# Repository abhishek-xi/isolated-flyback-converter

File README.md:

# Isolated Flyback Converter

## Overview

This repository contains the complete design of an isolated flyback DC-DC converter developed using KiCad. The project includes the schematic, PCB layout, manufacturing files, and supporting documentation required for fabrication and assembly.

The converter provides galvanic isolation between the input and output stages, making it suitable for embedded systems, industrial electronics, sensor interfaces, and low-power isolated supply applications.

---

## Features

- Isolated DC-DC power conversion
- Flyback converter topology
- Compact PCB design
- Designed using KiCad
- Manufacturing-ready Gerber files

---

## Design Files

| File | Description |
|--------|------------|
| prj1.kicad_sch | Circuit schematic |
| prj1.kicad_pcb | PCB layout |
| prj1.kicad_pro | KiCad project file |
| Gerbers | PCB manufacturing files |

---

## Applications

- Embedded Systems
- Industrial Electronics
- Sensor Interfaces
- Isolated Communication Systems
- Power Supply Modules
- IoT Devices

---

## Tools Used

- KiCad
- Git
- GitHub

---

## Future Improvements

- Transformer optimization
- Efficiency characterization
- Thermal analysis
- EMC/EMI validation
- Hardware testing documentation

---

## Author

**Abhishek B Kumbar**

Electronics and Communication Engineering

---

## License

This project is released under the MIT License.

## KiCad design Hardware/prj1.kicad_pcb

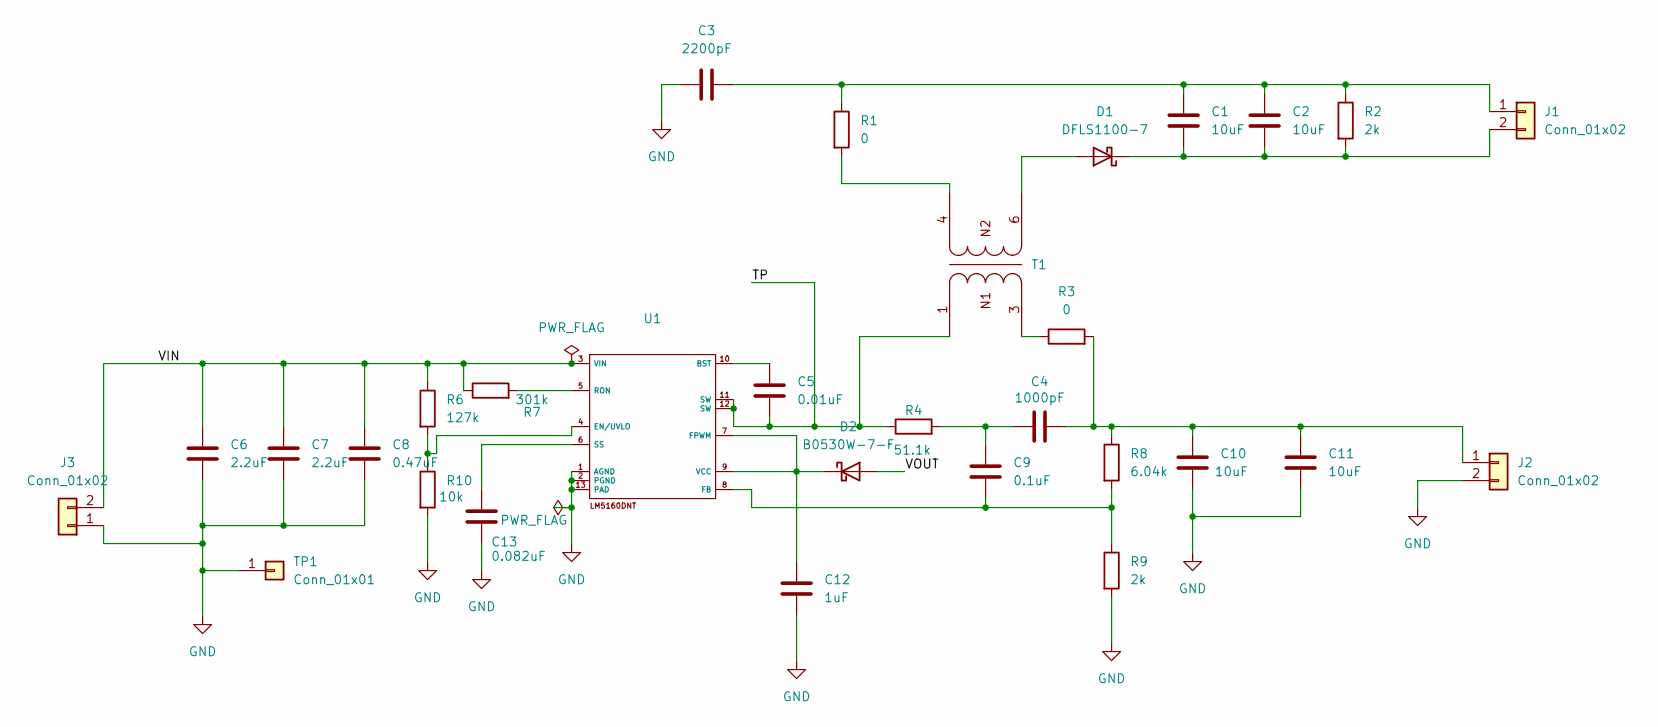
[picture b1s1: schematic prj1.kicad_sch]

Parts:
C1, C2, C10, C11: 10uF; C_1206_3216Metric
C3: 2200pF; C_0603_1608Metric
C4: 1000pF; C_0603_1608Metric
C5: 0.01uF; C_0603_1608Metric
C6, C7: 2.2uF; C_0805_2012Metric
C8: 0.47uF; C_0805_2012Metric
C9: 0.1uF; C_0603_1608Metric
C12: 1uF; C_0603_1608Metric
C13: 0.082uF; C_0603_1608Metric
D1: DFLS1100-7; D_SMA
D2: B0530W-7-F; D_SMA
J1, J2, J3: Conn_01x02; TerminalBlock_Phoenix_MKDS-1,5-2-5.08_1x02_P5.08mm_Horizont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
R1, R3: 0; R_0603_1608Metric
R2, R9: 2k; R_0603_1608Metric
R4: 51.1k; R_0603_1608Metric
R6: 127k; R_0603_1608Metric
R7: 301k; R_0603_1608Metric
R8: 6.04k; R_0603_1608Metric
R10: 10k; R_0603_1608Metric
T1: EP7_L10.16W13.36H8.64_750314597; T_Wurth_WE-IBTI-EP7_L10.16W13.36H8.64; Part Number 750314597
TP1: Conn_01x01; TestPoint_THTPad_1.5x1.5mm_Drill0.7mm
U1: SON50P400X400X100-13N

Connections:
/TP: C5.2, R4.1, T1.1, U1.11 (SW), U1.12 (SW)
/VIN: C6.1, C7.1, C8.1, J3.2, R6.1, R7.1, U1.3 (VIN)
/VOUT: D2.2 (A)
GND: C3.1, C6.2, C7.2, C8.2, C10.2, C11.2, C12.2, C13.2, J2.2, J3.1, R9.2, R10.2, TP1.1, U1.1 (AGND), U1.2 (PGND), U1.13 (PAD)
unnamed: C4.1, C9.1, R4.2
unnamed: D1.2 (A), T1.6
unnamed: C1.2, C2.2, D1.1 (K), J1.2, R2.2
unnamed: C12.1, D2.1 (K), U1.7 (FPWM), U1.9 (VCC)
unnamed: C1.1, C2.1, C3.2, J1.1, R1.1, R2.1
unnamed: C4.2, C10.1, C11.1, J2.1, R3.2, R8.1
unnamed: R1.2, T1.4
unnamed: R3.1, T1.3
unnamed: C5.1, U1.10 (BST)
unnamed: R6.2, R10.1, U1.4 (EN/UVLO)
unnamed: C9.2, R8.2, R9.1, U1.8 (FB)
unnamed: R7.2, U1.5 (RON)
unnamed: C13.1, U1.6 (SS)

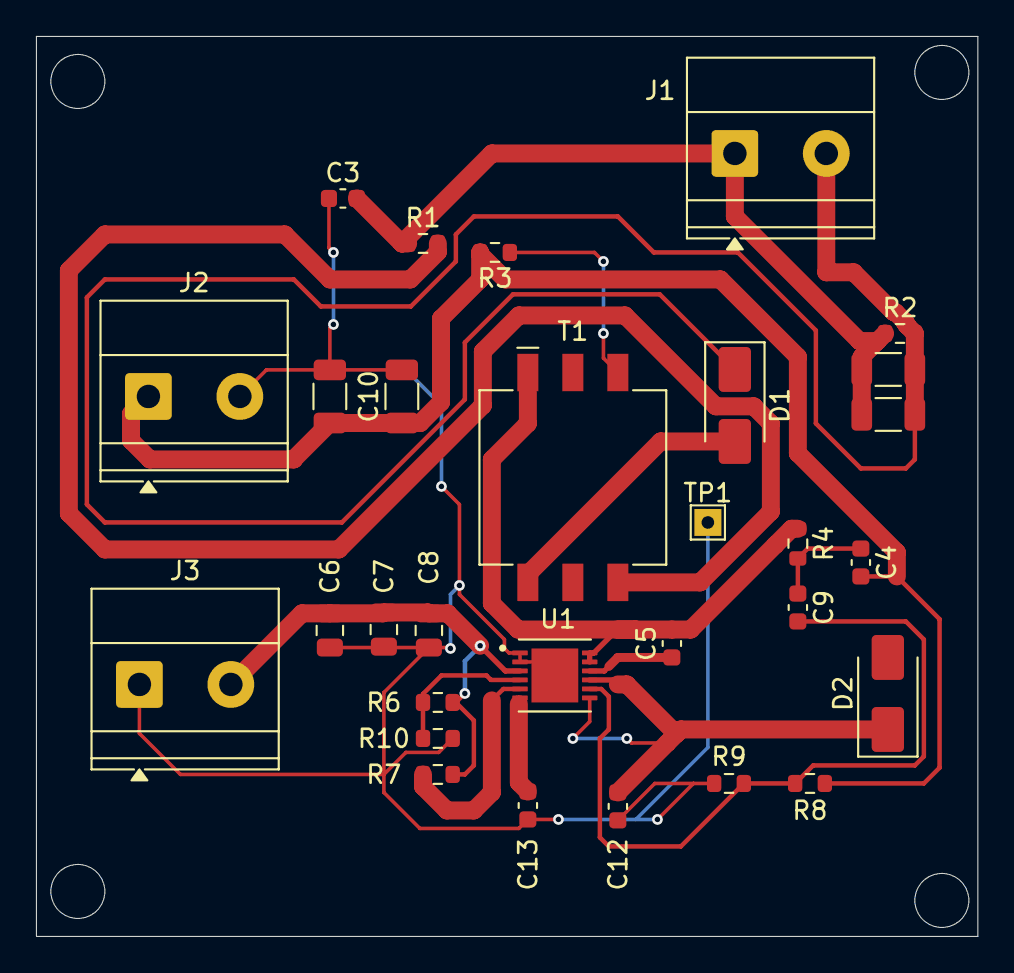
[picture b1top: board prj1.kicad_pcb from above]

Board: 2 copper layers, 52.3 x 50.0 mm, 30 parts (0 on the bottom side), 16 nets.

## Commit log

2026-05-29 Create LICENSE
